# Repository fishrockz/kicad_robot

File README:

after mush messing around i think i have got this so others can use it...

the kicad_robot needs to be in a directroy that also contains

https://github.com/fishrockz/kicad_robot_libary.git

https://github.com/XenGi/kicad_teensy.git

url = https://github.com/KiCad/kicad-library.git

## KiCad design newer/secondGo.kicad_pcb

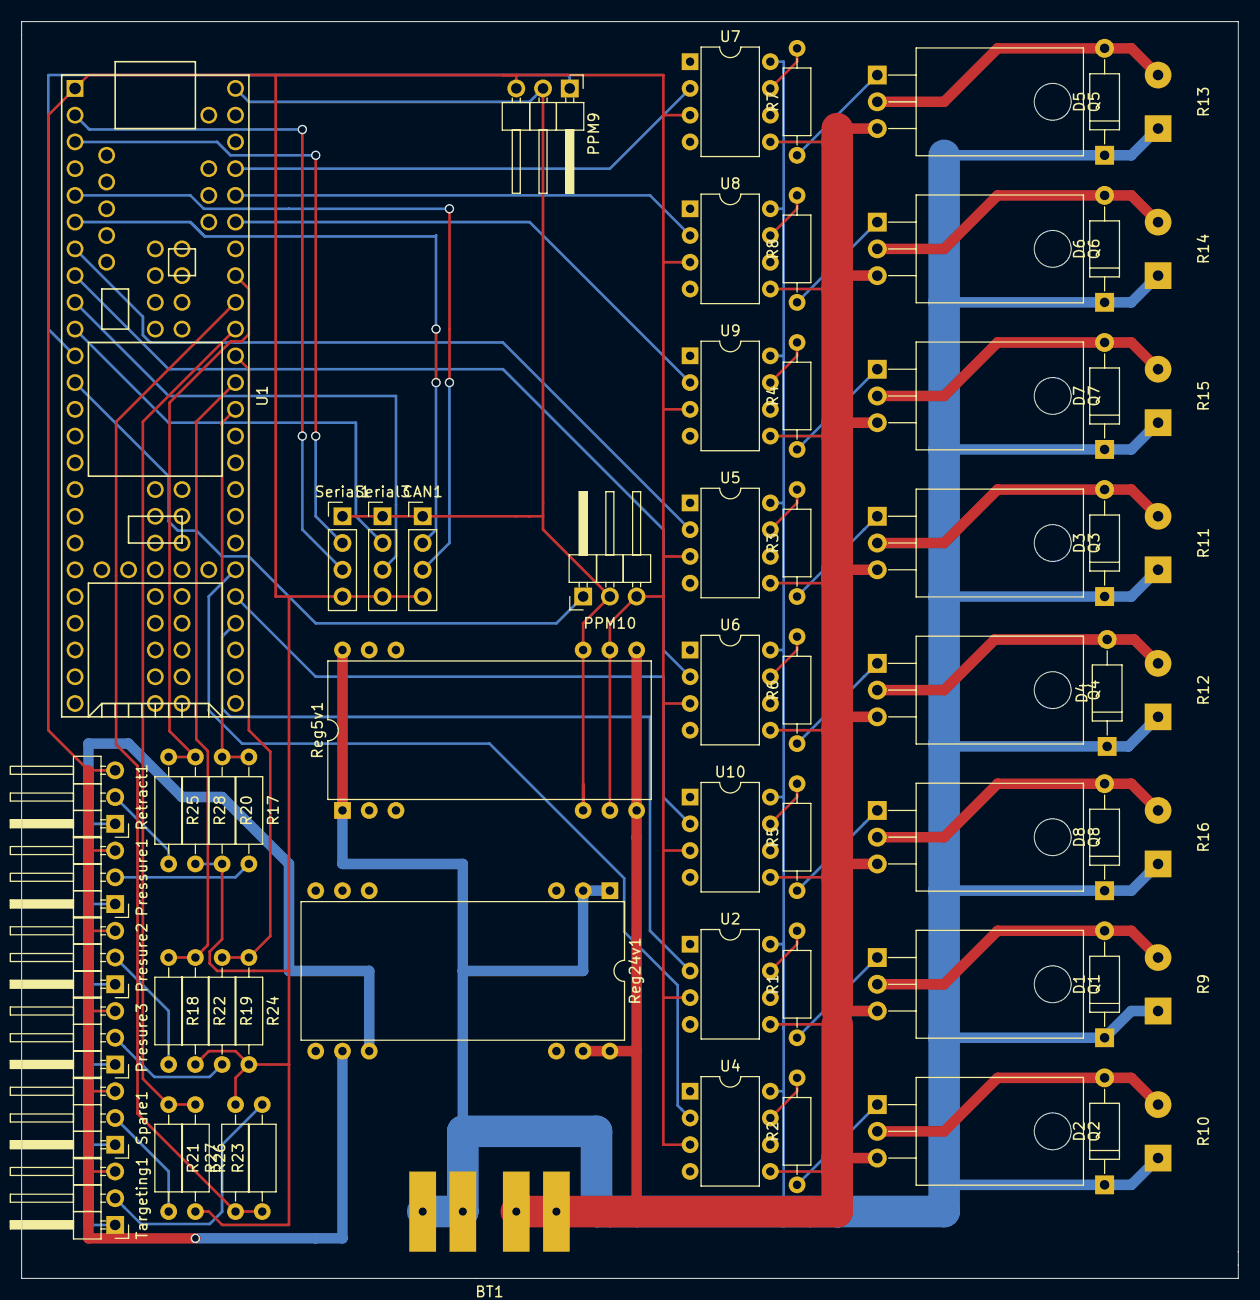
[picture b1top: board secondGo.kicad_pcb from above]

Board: 2 copper layers, 115.6 x 119.4 mm, 67 parts (0 on the bottom side), 57 nets.

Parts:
BT1: Battery; WSBattery
CAN1: CONN_01X04; Pin_Header_Straight_1x04_Pitch2.54mm
D1, D2, D3, D4, D5, D6, D7, D8: D; D_A-405_P10.16mm_Horizontal
PPM9, PPM10: CONN_01X03; Pin_Header_Angled_1x03_Pitch2.54mm
Pressure1: POT; Pin_Header_Angled_1x03_Pitch2.54mm
Presure2, Presure3: POT; Pin_Header_Angled_1x03_Pitch2.54mm
Q1, Q2, Q3, Q4, Q5, Q6, Q7, Q8: IRLZ34N; TO-220_Horizontal
R1, R2, R3, R4, R5, R6, R7, R8, R17, R18, R19, R20, R21, R22, R23, R24, R25, R26, R27, R28: R; R_Axial_DIN0207_L6.3mm_D2.5mm_P10.16mm_Horizontal
R9, R10, R11, R12, R13, R14, R15, R16: R; Value
Reg5v1: TRACO_DCDC_TEL_3-2411; traco_TEL_3-2411
Reg24v1: TRACO_DCDC_TVN_5-4815WI; traco_TVN_5-4815WI
Retract1: POT; Pin_Header_Angled_1x03_Pitch2.54mm
Serial1, Serial3: CONN_01X04; Pin_Header_Straight_1x04_Pitch2.54mm
Spare1: POT; Pin_Header_Angled_1x03_Pitch2.54mm
Targeting1: POT; Pin_Header_Angled_1x03_Pitch2.54mm
U1: Teensy3.5; Teensy35_36
U2, U4, U5, U6, U7, U8, U9, U10: HCPL3120; DIP-8_W7.62mm

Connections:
+24V: BT1.1, D1.1, D2.1, D3.1, D4.1, D5.1, D6.1, D7.1, D8.1, R9.1, R10.1, R11.1, R12.1, R13.1, R14.1, R15.1, R16.1, Reg5v1.1, Reg24v1.1, U2.8, U4.8, U5.8, U6.8, U7.8, U8.8, U9.8, U10.8
/Sheet58E8F73D/chanel1: U1.33, U2.2
/Sheet58E8F73D/chanel2: U1.35, U4.2
/Sheet58E8F73D/chanel3: U1.7, U5.2
/Sheet58E8F73D/chanel4: U1.8, U6.2
/Sheet58E8F73D/chanel6: U1.49, U8.2
/Sheet58E8F73D/chanel7: U1.48, U9.2
/Sheet58E8F73D/chanel8: U1.34, U10.2
/Sheet58E8F73D/changel5: U1.50, U7.2
/Sheet58E8F73D/cleanGND: CAN1.4, PPM9.3, PPM10.3, Pressure1.3, Presure2.3, Presure3.3, R20.2, R22.2, R24.2, R26.2, R27.2, R28.2, Reg5v1.11, Reg24v1.14, Retract1.3, Serial1.4, Serial3.4, Spare1.3, Targeting1.3, U1.1, U2.3, U4.3, U5.3, U6.3, U7.3, U8.3, U9.3, U10.3
GND: BT1.2, Q1.3, Q2.3, Q3.3, Q4.3, Q5.3, Q6.3, Q7.3, Q8.3, Reg5v1.12, Reg24v1.24, U2.5, U4.5, U5.5, U6.5, U7.5, U8.5, U9.5, U10.5
unnamed: CAN1.1, PPM9.2, PPM10.2, Reg5v1.10, Serial1.1, Serial3.1, U1.53
unnamed: CAN1.2, U1.6
unnamed: CAN1.3, U1.5
unnamed: D1.2, Q1.2, R9.2
unnamed: D2.2, Q2.2, R10.2
unnamed: D3.2, Q3.2, R11.2
unnamed: D4.2, Q4.2, R12.2
unnamed: D5.2, Q5.2, R13.2
unnamed: D6.2, Q6.2, R14.2
unnamed: D7.2, Q7.2, R15.2
unnamed: D8.2, Q8.2, R16.2
unnamed: PPM9.1, U1.11
unnamed: PPM10.1, U1.12
unnamed: Pressure1.1, Presure2.1, Presure3.1, Reg24v1.15, Retract1.1, Spare1.1, Targeting1.1
unnamed: Pressure1.2, R17.2
unnamed: Presure2.2, R18.2
unnamed: Presure3.2, R19.2
unnamed: Q1.1, R1.1
unnamed: Q2.1, R2.1
unnamed: Q3.1, R3.1
unnamed: Q4.1, R6.1
unnamed: Q5.1, R7.1
unnamed: Q6.1, R8.1
unnamed: Q7.1, R4.1
unnamed: Q8.1, R5.1
unnamed: R1.2, U2.7
unnamed: R2.2, U4.7
unnamed: R3.2, U5.7
unnamed: R4.2, U9.7
unnamed: R5.2, U10.7
unnamed: R6.2, U6.7
unnamed: R7.2, U7.7
unnamed: R8.2, U8.7
unnamed: R17.1, R20.1, U1.41
unnamed: R18.1, R22.1, U1.42
unnamed: R19.1, R24.1, U1.43
unnamed: R21.1, R26.1, U1.44
unnamed: R21.2, Spare1.2
unnamed: R23.1, R27.1, U1.45
unnamed: R23.2, Targeting1.2
unnamed: R25.1, R28.1, U1.46
unnamed: R25.2, Retract1.2
unnamed: Serial1.2, U1.3
unnamed: Serial1.3, U1.2
unnamed: Serial3.2, U1.10
unnamed: Serial3.3, U1.9

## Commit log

2017-04-08 basics of a single channel
2017-04-08 fogot the .pro
2017-04-08 Readme
2017-04-08 reff to other lib
2017-04-08 test
2017-04-08 README update
2017-04-08 POC traco
2017-04-08 switched to version 4 of kicad...
2017-04-08 more messing araound to get kicad 4 happy
2017-04-08 i feel like i am making a little progress again
2017-04-08 thats a full loay out :) only 3 channels and lots of bits missing but it shows the idea
2017-04-08 8 chanels, not finished
2017-04-09 much neater layout :) but only sorted the first 3 chanels, but the concept works
2017-04-10 big board but dosent look tooo bad
2017-04-13 more mods
2017-04-18 move the two versions in to to directorys
2017-04-18 trying to see if ican get it to fin in alexs space
2017-04-23 first version with the 3.5
2017-04-23 little fixes
2017-04-23 more little fixes
2017-04-23 long board idea started
2017-04-23 first version of the long board concept, its not great but it looks ok from a quick look
2017-04-23 more updates
2017-05-05 moved long board in to new folder as kicad was crashing
